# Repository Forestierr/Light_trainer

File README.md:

<h1 align="center">⚡ Light Trainer — Système d'Entraînement Réactif Sans Fil ⚡</h1>

<p align="center">

</p>

<p align="center">
  <b>Pods lumineux interactifs, ultra-réactifs et modulaires pour l'entraînement sportif, le travail des réflexes, de l'agilité et de la réactivité cognitive.</b>
</p>

---

## 🌟 Points Forts du Système

* 🚀 **Zéro Latence & Réseau Maillé Auto-Organisé** : Communication instantanée multi-sauts via **ESP-NOW (2.4 GHz)**. Pas besoin de routeur Wi-Fi, les pods se découvrent et se synchronisent automatiquement.
* ✋ **Interaction 100% Sans Contact (ToF Laser)** : Télémètre **VL53L0X** cadencé à 50 Hz pour une détection millimétrique des frappes sans usure mécanique.
* 🌈 **Affichage 360° Haute Visibilité** : Anneau de 7 LEDs RVB adressables **WS2812B** avec gestion de jauges de progression et flashs de confirmation.
* 🔋 **Gestion d'Énergie Avancée & Autonomie** :
  * Batterie LiPo 3.7V avec **recharge USB-C automatique**.
  * **Deep Sleep ultra-basse consommation ($\approx 10\,\mu\text{A}$)** via coupure d'alimentation commutée $3\text{V}3\_S$ et réveil instantané sur interrupteur.
  * Mesure continue de la tension de batterie avec compensation ADC d'usine eFuse.
* 📱 **Double Interface** : Pilotage 100% gestuel sur le pod + portail Web de configuration intégré (Wi-Fi SoftAP).

---

## 📂 Structure du Répertoire

```
Light_trainer/
├── 1_Documentation/               # 📖 Documentation complète & schémas
│   ├── Architecture_Systeme.md    # Spécifications techniques & protocoles
│   ├── Dashboard_Web_App.md       # Spécifications de l'interface Web & API
│   ├── Guide_Montage_Materiel.md  # Guide pas-à-pas d'assemblage & BOM
│   ├── Manuel_Utilisation_et_Modes.md # Guide des gestes & 5 modes de jeu
│   ├── Roadmap_Idees_et_TODO.md   # Feuille de route & TODO pour la production
│   └── DOC_FAB/schema.pdf         # Schéma électronique officiel V3
├── 2_Mesures/                     # 📊 Cahier d'expérimentation & banc d'essais
│   └── Protocole_de_Tests_et_Mesures.md # Tableaux de relevés et qualification
├── 3_Datasheets/                  # 📑 Fiches techniques des composants
├── 4_Fabrication/                 # 🛠️ Fichiers de fabrication KiCad & Gerber
│   └── Version_02/light_trainer/  # Projet PCB KiCad V3
├── 5_Programmation/               # 💻 Codes sources & firmware
│   ├── XIAO-esp32-v3/main/        # Firmware principal complet (Production)
│   └── TEST_BENCH/                # Suite de qualification unitaire matérielle
└── README.md                      # Ce document
```

---

## 📐 Schéma & Câblage Matériel (V3 / Veroboard)

### Pinout du Seeed Studio XIAO ESP32-C3

```
                       +-------------------+
                       |    [ USB-C ]      |
     (ADC Batt)   D1 --| 2              14 |-- 5V VBUS  (Détection Charge USB)
   (Switch SW1)   D2 --| 3              13 |-- GND      (Masse Commune)
  (Buzzer Opt.)   D3 --| 4              12 |-- 3V3_OUT  (Sortie Régulateur LDO)
     (I2C SCL)    D4 --| 5              11 |-- D10      (Entrée Diviseur Charge)
     (I2C SDA)    D5 --| 6              10 |-- D9
                  D6 --| 7               9 |-- D8
    (LED Data)    D7 --| 8               8 |-- 3V3
                       +-------------------+
                          |  [BAT+]  [GND] |
                          |   (21)    (22) |
```

> [!TIP]
> **Résistances $100\text{ k}\Omega$ Unifiées** : Le circuit utilise uniquement des résistances standard de **$100\text{ k}\Omega$** ($R_1$ à $R_6$), simplifiant l'approvisionnement et le montage.

Consultez le [**Guide de Montage Matériel**](file:///c:/Users/Robin/Desktop/GitHub/Light_trainer/1_Documentation/Guide_Montage_Materiel.md) pour les détails d'implantation et les schémas complets.

---

## 🎮 Modes de Jeu & Navigation Gestuelle

| Geste ToF | Durée | Action en Mode Menu | Action en Cours de Jeu |
| :--- | :--- | :--- | :--- |
| **Tap Court** | $< 500\text{ ms}$ | Défilement des 5 modes (0 $\rightarrow$ 1 $\rightarrow$ 2 $\rightarrow$ 3 $\rightarrow$ 4 $\rightarrow$ 0) | *Ignoré* |
| **Hold Départ** | $1.5\text{ s}$ | **Départ de partie** (Jauge circulaire 0 à 100%) | *Non applicable* |
| **Frappe (Hit)** | $< 300\text{ ms}$ | *Ignoré* | **Validation de la cible** (Flash blanc instantané) |
| **Hold Menu** | $3.0\text{ s}$ | *Réinitialisation* | **Arrêt du jeu** et retour synchronisé au Menu pour tout le réseau |

Consultez le [**Manuel d'Utilisation**](file:///c:/Users/Robin/Desktop/GitHub/Light_trainer/1_Documentation/Manuel_Utilisation_et_Modes.md) pour découvrir les **5 modes sportifs** disponibles (Vitesse Solo, Duel Bicolore, Réflexe Aléatoire, Agilité Cognitive et Jeu Simon).

---

## 🧪 Banc de Tests et Qualification

Un firmware dédié autonome [`5_Programmation/TEST_BENCH/TEST_BENCH.ino`](file:///c:/Users/Robin/Desktop/GitHub/Light_trainer/5_Programmation/TEST_BENCH/TEST_BENCH.ino) permet de mesurer précisément les performances de votre prototype :

1. `TEST_BATTERY_STRESS` : Décharge extrême à pleine puissance (LEDs 100% blanches + RF) avec export CSV.
2. `TEST_BATTERY_GAME_SIM` : Test d'autonomie en conditions de match réelles.
3. `TEST_TOF_BENCHMARK` : Test de portée ToF, cadence de frappe (hits/min) et tenue aux perturbations solaires.
4. `TEST_RADIO_PING_RTT_RSSI` : Mesure de la portée radio, de la latence RTT (ms) et de la force du signal (RSSI).
5. `TEST_DEEP_SLEEP_POWER` : Validation de l'interrupteur matériel et mesure du courant de veille.
6. `TEST_ALL_INTERACTIVE` : Tableau de bord interactif par commandes Série.

---

## 🚀 Démarrage Rapide

### Prérequis Logiciels
* [Arduino IDE](https://www.arduino.cc/en/software) (version 2.x recommandée).
* Package de cartes : **ESP32 by Espressif Systems** (version 2.0.14+ ou 3.x).
* Sélectionner la carte : **`XIAO_ESP32C3`**.
* **Configuration Indispensable de la Flash** :
  > [!IMPORTANT]
  > Dans le menu **Outils $\rightarrow$ Partition Scheme**, sélectionnez impérativement **`Huge APP (3MB No OTA/1MB SPIFFS)`**.
  > La puce physique du XIAO ESP32-C3 dispose de 4 Mo de Flash. Sans ce réglage, le schéma standard réserve seulement 1.3 Mo à l'application, ce qui est insuffisant pour accueillir l'interface Web complète et provoque une erreur de compilation *`Sketch too big`*.
* Bibliothèques Arduino requises :
  * `FastLED`
  * `Adafruit_VL53L0X`

### Flasher le Projet
1. Ouvrez [`5_Programmation/XIAO-esp32-v3/main/main.ino`](file:///c:/Users/Robin/Desktop/GitHub/Light_trainer/5_Programmation/XIAO-esp32-v3/main/main.ino).
2. Branchez le XIAO ESP32-C3 via un câble USB-C.
3. Vérifiez que la carte est bien configurée en **Huge APP (3MB)**.
4. Cliquez sur **Téléverser**.
5. Ouvrez le Moniteur Série à **115200 bauds** pour observer le tableau de bord temps réel.

---

## 🗺️ Feuille de Route & Production

Pour découvrir les axes d'évolution logicielle pour le déploiement à grande échelle (SoftAP master exclusif, WebSockets, Gzip, PWA, calibration ToF, Web OTA et PlatformIO), consultez notre [**Feuille de Route & TODO Backlog**](file:///c:/Users/Robin/Desktop/GitHub/Light_trainer/1_Documentation/Roadmap_Idees_et_TODO.md).

---

## 📄 Licence

Ce projet est distribué sous licence **Apache 2.0**. Consultez le fichier [`LICENSE`](file:///c:/Users/Robin/Desktop/GitHub/Light_trainer/LICENSE) pour plus de détails.

---
<p align="center"><i>Robin Forestier — Projet Light Trainer</i></p>

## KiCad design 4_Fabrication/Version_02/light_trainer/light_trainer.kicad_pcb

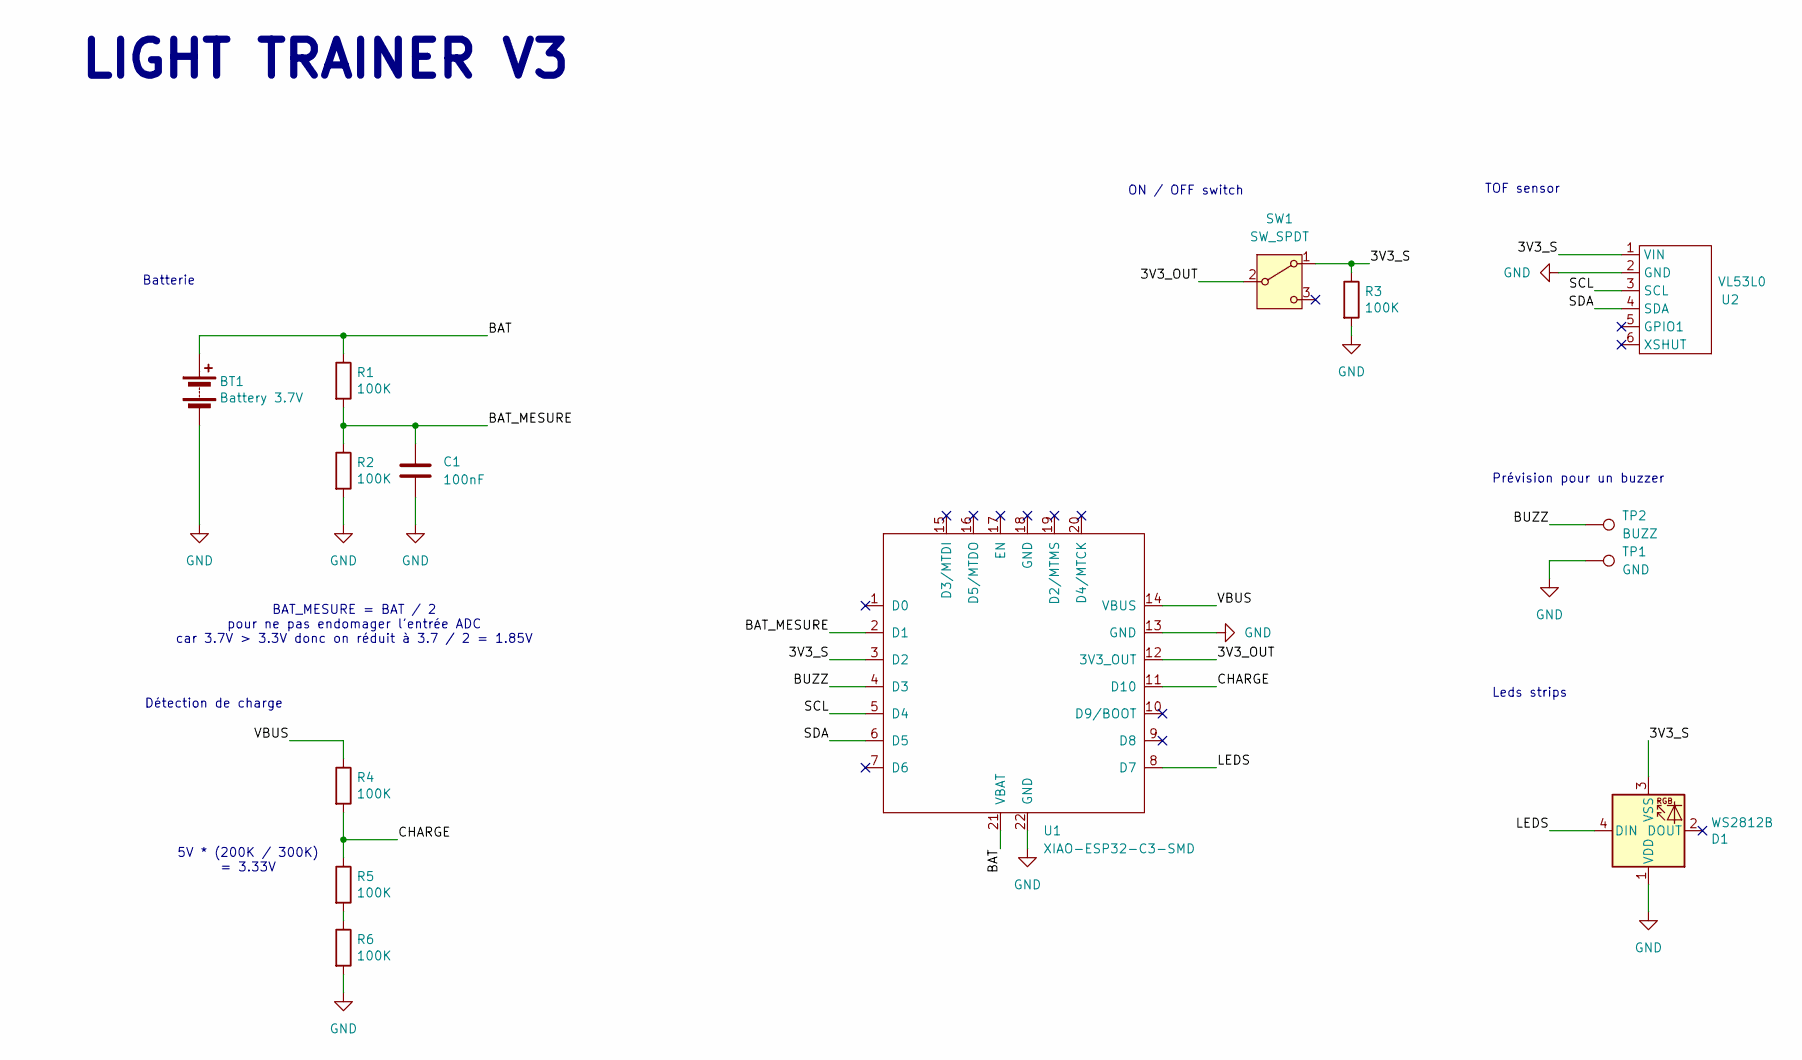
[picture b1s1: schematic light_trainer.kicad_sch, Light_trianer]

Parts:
BT1: Battery 3.7V; PinHeader_1x02_P2.54mm_Vertical
C1: 100nF; CP_Radial_D5.0mm_P2.50mm
D1: WS2812B; PinHeader_1x04_P2.54mm_Vertical
R1, R2, R3, R4, R5, R6: 100K; R_Axial_DIN0207_L6.3mm_D2.5mm_P7.62mm_Horizontal
SW1: SW_SPDT; PinSocket_1x03_P2.54mm_Vertical
TP1: GND; PinHeader_1x01_P2.54mm_Vertical
TP2: BUZZ; PinHeader_1x01_P2.54mm_Vertical
U1: XIAO-ESP32-C3-SMD; XIAO-ESP32-C3-DIP-SMD
U2: VL53L0

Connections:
/3V3_OUT: SW1.2 (B), U1.12 (3V3_OUT)
/3V3_S: D1.3 (VSS), R3.1, SW1.1 (A), U1.3 (D2), U2.1 (VIN)
/BAT: BT1.1 (+), R1.1, U1.21 (VBAT)
/BAT_MESURE: C1.1, R1.2, R2.1, U1.2 (D1)
/BUZZ: TP2.1 (1_1), U1.4 (D3)
/CHARGE: R4.2, R5.1, U1.11 (D10)
/LEDS: D1.4 (DIN), U1.8 (D7)
/SCL: U1.5 (D4), U2.3 (SCL)
/SDA: U1.6 (D5), U2.4 (SDA)
/VBUS: R4.1, U1.14 (VBUS)
GND: BT1.2 (-), C1.2, D1.1 (VDD), R2.2, R3.2, R6.2, TP1.1 (1_1), U1.13 (GND), U1.22 (GND), U2.2 (GND)
unnamed: R5.2, R6.1

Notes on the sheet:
ON / OFF switch
Détection de charge
Prévision pour un buzzer
5V * (200K / 300K) = 3.33V
LIGHT TRAINER V3
Leds strips
BAT_MESURE = BAT / 2 pour ne pas endomager l'entrée ADC car 3.7V > 3.3V donc on réduit à 3.7 / 2 = 1.85V
Batterie
TOF sensor

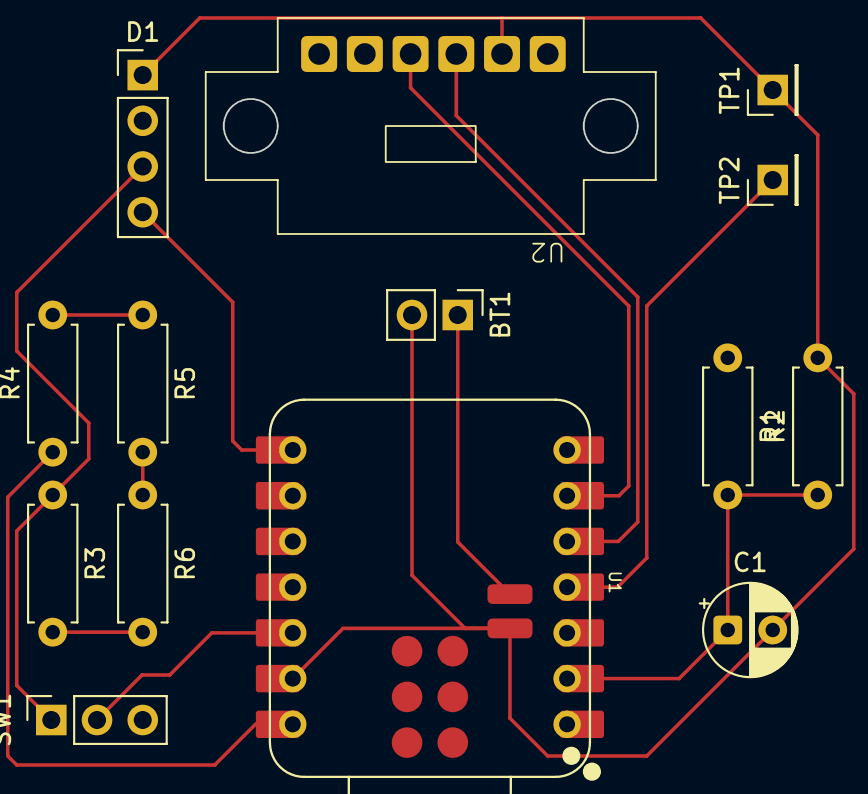
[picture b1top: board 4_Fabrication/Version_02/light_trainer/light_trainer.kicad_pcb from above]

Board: 2 copper layers, 14 parts (0 on the bottom side), 12 nets.

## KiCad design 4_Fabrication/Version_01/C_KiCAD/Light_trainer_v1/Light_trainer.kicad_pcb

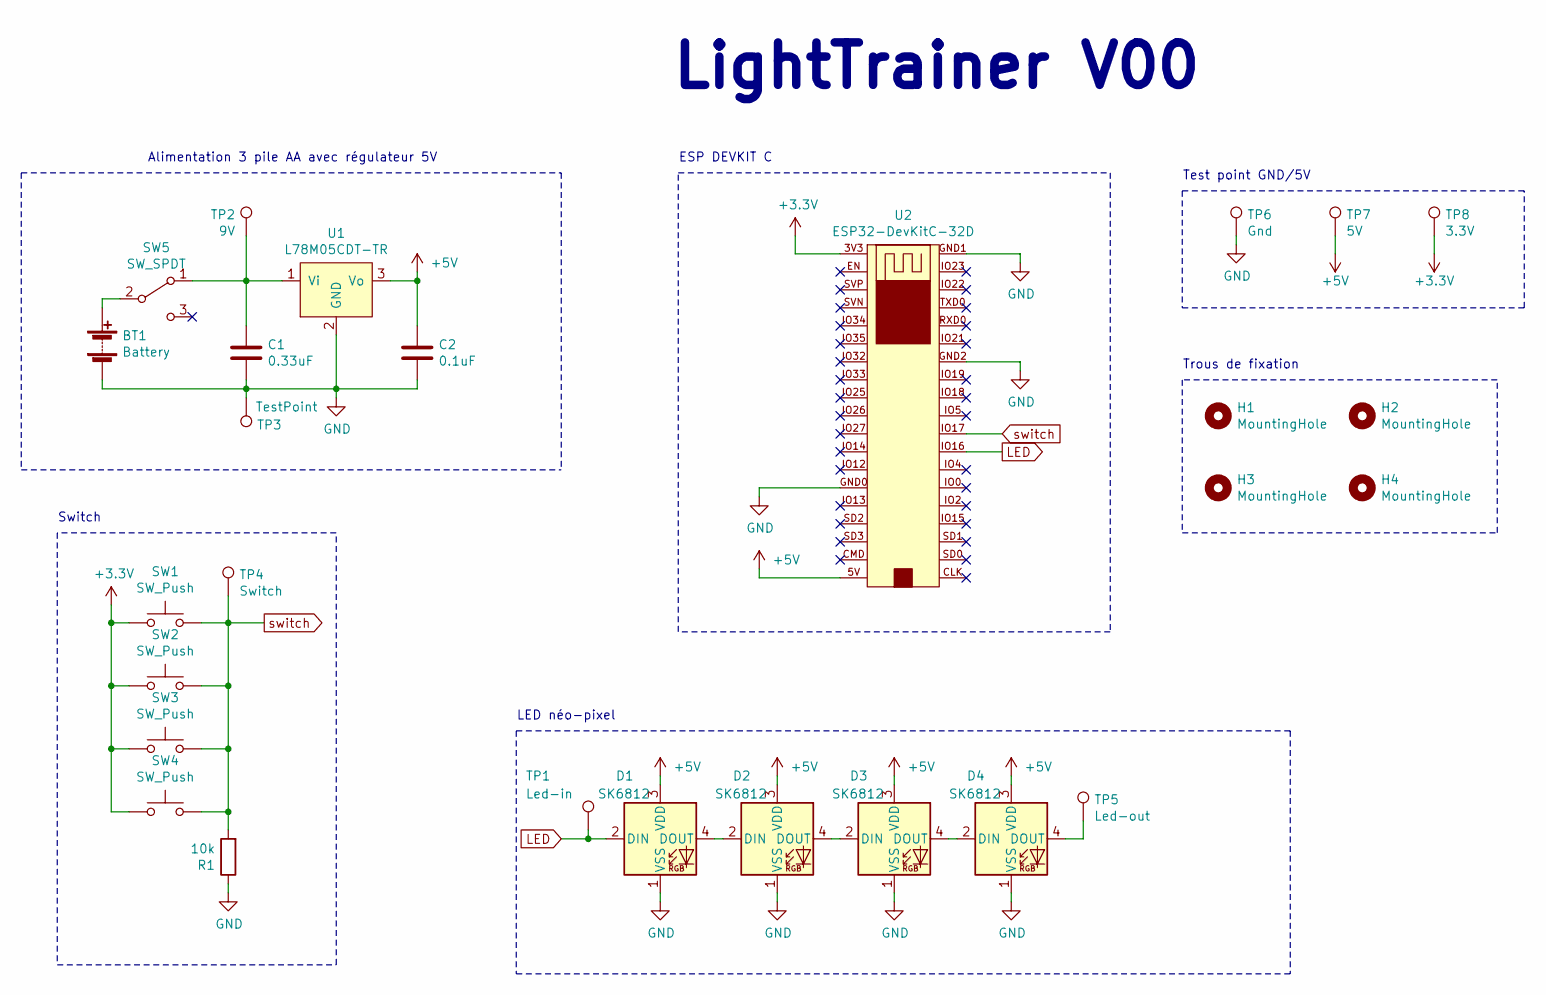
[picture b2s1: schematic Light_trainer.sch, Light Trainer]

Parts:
BT1: Battery; BatteryHolder_Keystone_593-594
C1: 0.33uF; C_0805_2012Metric
C2: 0.1uF; C_0805_2012Metric
D1, D2, D3, D4: SK6812; LED_SK6812_PLCC4_5.0x5.0mm_P3.2mm
H1, H2, H3, H4: MountingHole; MountingHole_3.2mm_M3
R1: 10k; R_1206_3216Metric
SW1, SW2, SW3, SW4: SW_Push; SW_Cherry_MX_1.00u_PCB_3D
SW5: SW_SPDT; C&K-1101M2S5CQE2
TP1: Led-in; TestPoint_THTPad_2.5x2.5mm_Drill1.2mm
TP2: 9V; TestPoint_THTPad_2.5x2.5mm_Drill1.2mm
TP3: TestPoint; TestPoint_THTPad_2.5x2.5mm_Drill1.2mm
TP4: Switch; TestPoint_THTPad_2.5x2.5mm_Drill1.2mm
TP5: Led-out; TestPoint_THTPad_2.5x2.5mm_Drill1.2mm
TP6: Gnd; TestPoint_THTPad_2.5x2.5mm_Drill1.2mm
TP7: 5V; TestPoint_THTPad_2.5x2.5mm_Drill1.2mm
TP8: 3.3V; TestPoint_THTPad_2.5x2.5mm_Drill1.2mm
U1: L78M05CDT-TR; TO-252-2
U2: ESP32-DevKitC-32D

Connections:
+3V3: SW1.1, SW2.1, SW3.1, SW4.1, TP8.1, U2.3V3
+5V: C2.1, D1.3 (VDD), D2.3 (VDD), D3.3 (VDD), D4.3 (VDD), TP7.1, U1.3 (Vo), U2.5V
GND: BT1.2 (-), C1.2, C2.2, D1.1 (VSS), D2.1 (VSS), D3.1 (VSS), D4.1 (VSS), R1.1, TP3.1, TP6.1, U1.2 (GND), U2.GND0, U2.GND1, U2.GND2
LED: D1.2 (DIN), TP1.1, U2.IO16
unnamed: BT1.1 (+), SW5.2 (B)
unnamed: C1.1, SW5.1 (A), TP2.1, U1.1 (Vi)
unnamed: D1.4 (DOUT), D2.2 (DIN)
unnamed: D2.4 (DOUT), D3.2 (DIN)
unnamed: D3.4 (DOUT), D4.2 (DIN)
unnamed: D4.4 (DOUT), TP5.1
switch: R1.2, SW1.2, SW2.2, SW3.2, SW4.2, TP4.1, U2.IO17

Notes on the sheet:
Switch
LightTrainer V00
LED néo-pixel
ESP DEVKIT C
Alimentation 3 pile AA avec régulateur 5V
Test point GND/5V
Trous de fixation

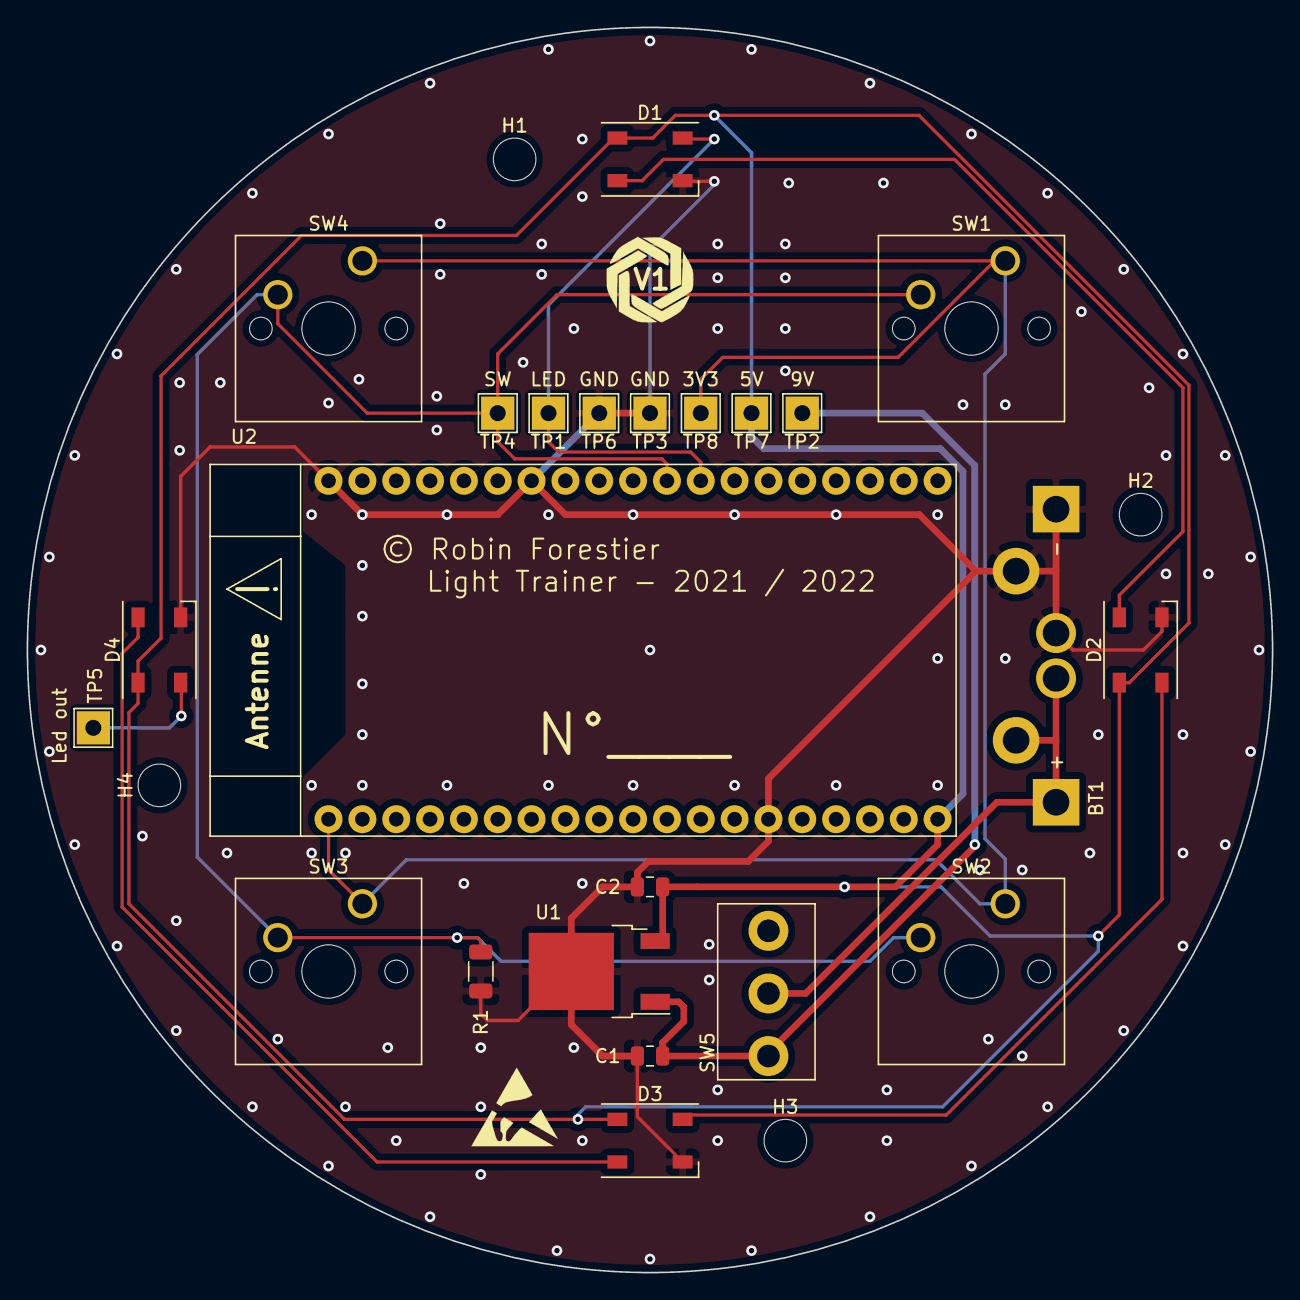
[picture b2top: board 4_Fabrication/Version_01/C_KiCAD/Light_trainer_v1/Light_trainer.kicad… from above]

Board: 2 copper layers, 93.5 x 93.5 mm, 27 parts (0 on the bottom side), 11 nets.

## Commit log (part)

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2020-11-27 fisrts commit
    creation folder
2020-11-27 add site
    création premier version du site
2020-11-28 liste des pièce
    add liste de pièce + 3d
2020-11-29 update 3d
    3d test v1
2020-11-30 Create LICENSE
2020-12-05 add image + 3d
    Add image, 3d conn_1, modif fichier
2020-12-08 add kicad
    add first kicad + modif readme
2020-12-09 modif kicad
2020-12-15 modif kicad
    add programateur, protection, esd
2020-12-16 add neo-pixel led
    add néo-pixel led
    add 3V to 5V
    modif condo EN
    add listes des composants
2020-12-19 add label
2021-01-04 modif KiCad
    modif protect batt
    change usb driver
    add data sheet and foot print
2021-01-05 modif kicad
    first layout
    8 néo pixel
2021-01-17 add release
2021-01-17 add esp-32
2021-06-22 add code
    I maybe want to work with pi pico and NRF24l01.
    But I have to abandoned my idea of the site web.
2021-09-11 add datasheet
    Restart the project
2021-09-12 add footprint
2021-09-12 ADD all footprint
    All footprint
    miss 1 3d (battery holder 3xAA)
2021-09-12 add all 3D
2021-09-13 first routage
    first placement + start routage
2021-09-14 placement + routage
2021-09-15 Creat Gerber
    creation des fichiers gerber.
2021-09-15 add pdf fabrication
    add pdf fabrication
2021-09-15 add pdf DOC FAB
2021-09-15 Add img for wiki
2021-09-15 add liste panier
2021-09-17 creat archive
    creat archive V1
2021-10-11 add programmation
2022-02-02 new prog
2022-06-15 new site + new logo
2022-06-15 new pcb
2022-06-17 new prog !
2026-02-05 Add ESP32 Light Trainer (XIAO) project
    Introduce a complete ESP32 (XIAO) Light Trainer project implementing a multiplayer game system. Adds core modules: Hardware (WS2812B LED and VL53L0X sensor handling), GameNetwork (ESP-NOW peer discov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
2026-02-05 Refactor GameEngine/Hardware; add battery support
    Major refactor across GameEngine, Hardware and GameNetwork plus docs update:
    - Config.h: add NVS brightness key, default brightness, battery monitoring config (divider, ADC pin, thresholds), reorder debug levels and add CMD_RETURN_TO_MENU.
    - GameEngine: move initial state to constructor, implement non-blocking startGame sequence, add returnToMenu and long-press menu trigger handling, use getters for modes/IDs, adapt scheduling/activati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
    - GameNetwork: encapsulate myId and known nodes (fixed-size array), add getMyId/getKnownNodes, make addNode return bool, robust MAC conversion helper and peer-add erro

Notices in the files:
4_Fabrication/Version_00/C_KiCAD/Light_trainer/Light_trainer.sch:
©2021 Robin Forestier
4_Fabrication/Version_01/C_KiCAD/Light_trainer_v1/Light_trainer.kicad_pcb:
©Robin Forestier | 2021
4_Fabrication/Version_01/C_KiCAD/Light_trainer_v1/Light_trainer.sch:
©2022 Robin Forestier
README.md:
License: Apache 2.0
